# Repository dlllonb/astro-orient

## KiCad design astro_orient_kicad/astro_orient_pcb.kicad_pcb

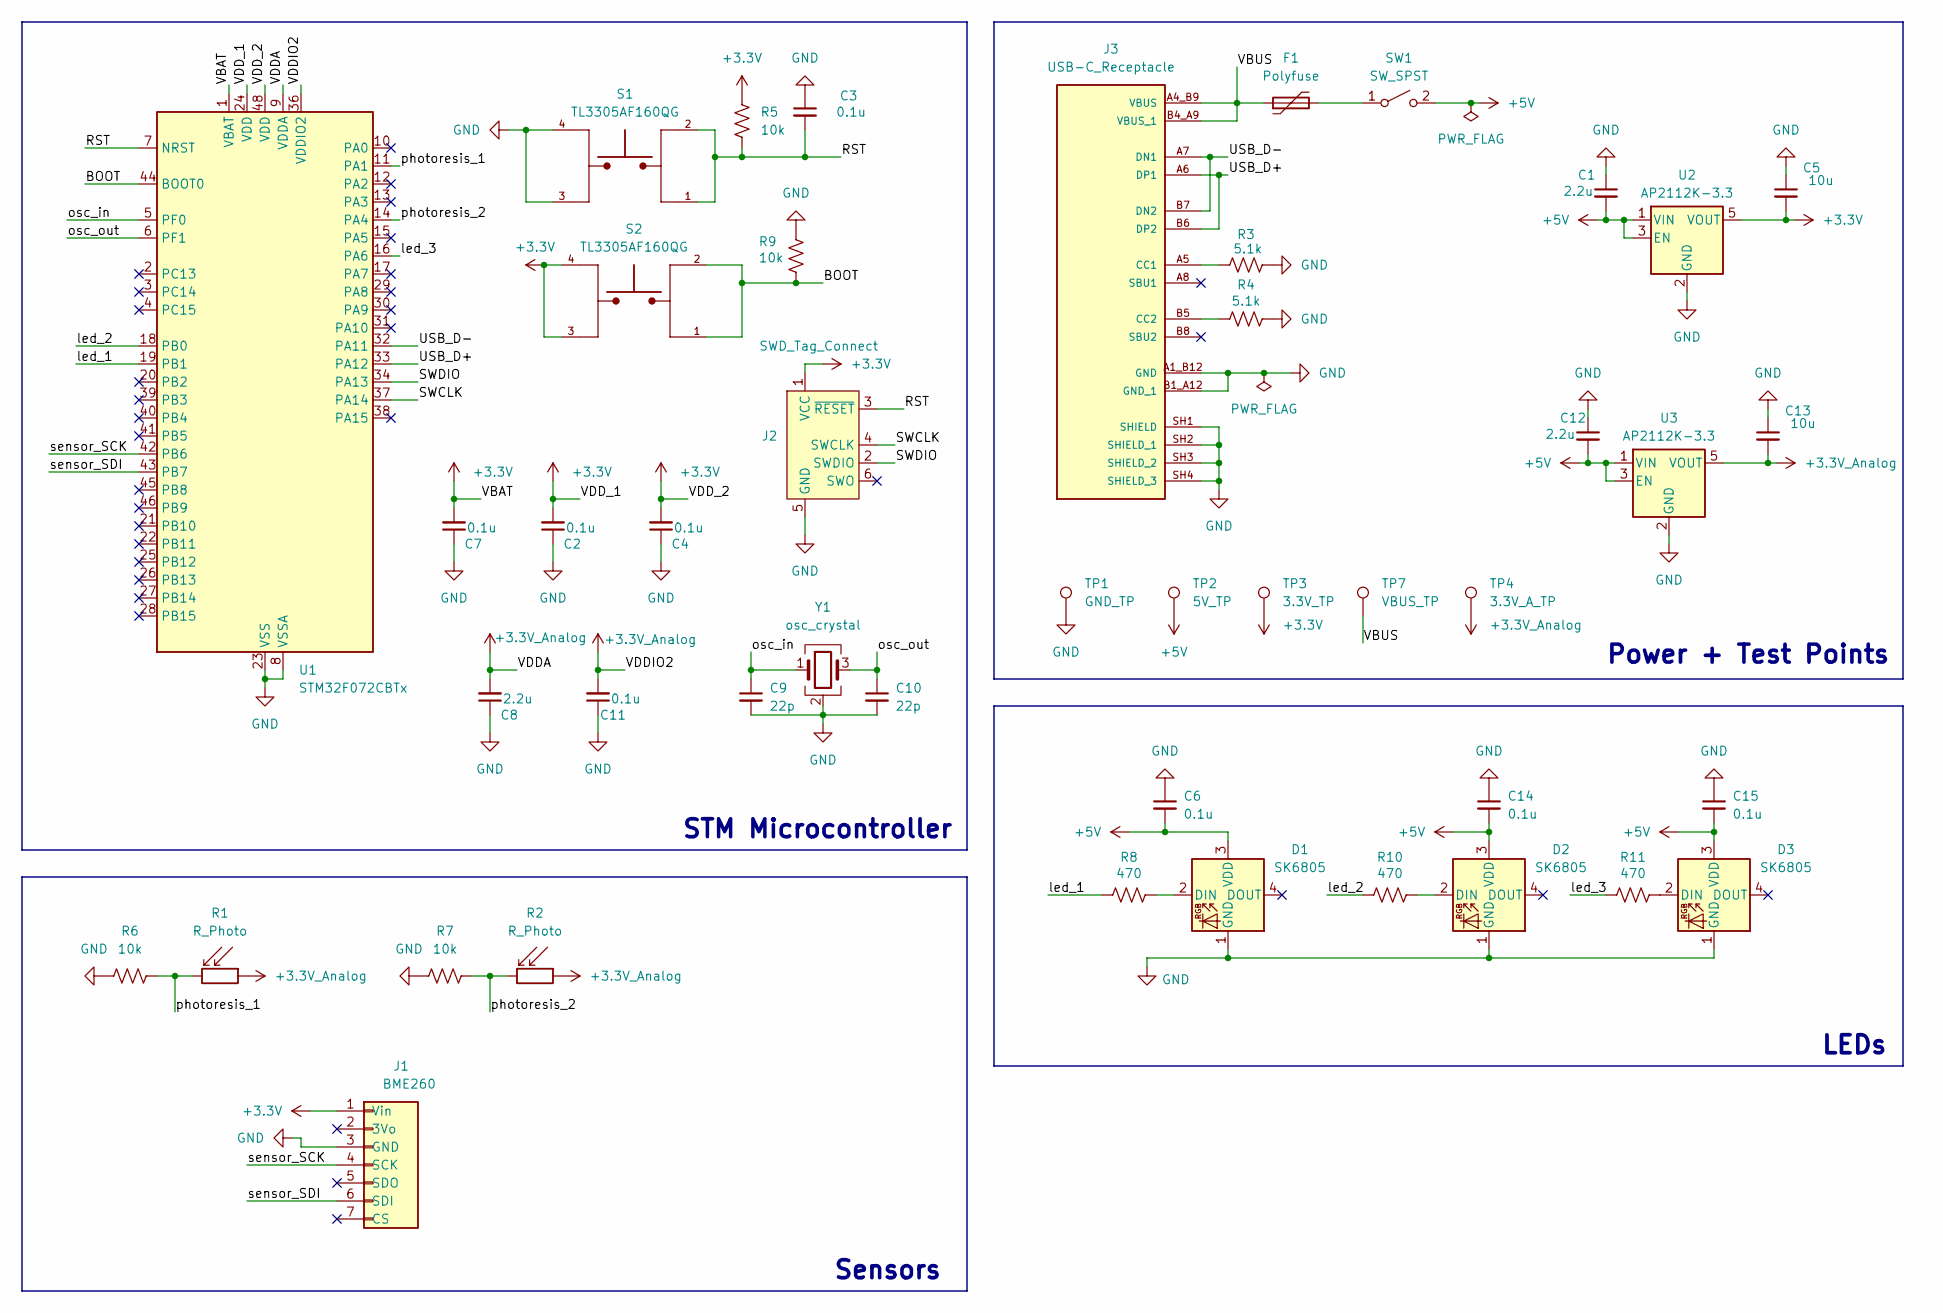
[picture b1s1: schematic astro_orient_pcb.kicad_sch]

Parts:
C1, C8, C12: 2.2u; C_0805_2012Metric
C2, C3, C4, C6, C7, C11, C14, C15: 0.1u; C_0805_2012Metric
C5, C13: 10u; C_1206_3216Metric
C9, C10: 22p; C_0805_2012Metric
D1: SK6805; LED_1655
D2, D3: SK6805; PinHeader_1x04_P2.54mm_Vertical
F1: Polyfuse; Fuse_1812_4532Metric
J1: BME260; PinHeader_1x07_P2.54mm_Vertical
J2: SWD_Tag_Connect; Tag-Connect_TC2030-IDC-FP_2x03_P1.27mm_Vertical
J3: USB-C_Receptacle; SAMESKY_UJ20-C-H-G-SMT-1-P16-TR_Correct; PARTREV 1.0
R1, R2: R_Photo; PHODET_PDV-P8103
R3, R4: 5.1k; R_0805_2012Metric
R5, R6, R7, R9: 10k; RC0805N_YAG-L
R8, R10, R11: 470; R_2512_6332Metric
S1, S2: TL3305AF160QG; SW_TL3305AF160QG; PARTREV C
SW1: SW_SPST; PinHeader_1x02_P2.54mm_Vertical
TP1: GND_TP; TestPoint_Pad_D1.0mm
TP2: 5V_TP; TestPoint_Pad_D1.0mm
TP3: 3.3V_TP; TestPoint_Pad_D1.0mm
TP4: 3.3V_A_TP; TestPoint_Pad_D1.0mm
TP7: VBUS_TP; TestPoint_Pad_D1.0mm
U1: STM32F072CBTx; LQFP-48_7x7mm_P0.5mm
U2, U3: AP2112K-3.3; SOT95P285X140-5N
Y1: osc_crystal; Crystal_SMD_Abracon_ABM3B-4Pin_5.0x3.2mm

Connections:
+3.3V: C2.2, C4.2, C5.2, C7.2, J1.1 (Vin), J2.1 (VCC), R5.1, S2.3, S2.4, TP3.1, U1.1 (VBAT), U1.24 (VDD), U1.48 (VDD), U2.5 (VOUT)
+3.3V_Analog: C8.2, C11.2, C13.2, R1.1, R2.1, TP4.1, U1.9 (VDDA), U1.36 (VDDIO2), U3.5 (VOUT)
+5V: C1.2, C6.2, C12.2, C14.2, C15.2, D1.3 (VDD), D2.3 (VDD), D3.3 (VDD), SW1.2 (B), TP2.1, U2.1 (VIN), U2.3 (EN), U3.1 (VIN), U3.3 (EN)
/BOOT: R9.2, S2.1, S2.2, U1.44 (BOOT0)
/RST: C3.2, J2.3 (~RESET), R5.2, S1.1, S1.2, U1.7 (NRST)
/SWCLK: J2.4 (SWCLK), U1.37 (PA14)
/SWDIO: J2.2 (SWDIO), U1.34 (PA13)
/USB_D+: J3.A6 (DP1), J3.B6 (DP2), U1.33 (PA12)
/USB_D-: J3.A7 (DN1), J3.B7 (DN2), U1.32 (PA11)
/VBUS: F1.1, J3.A4_B9 (VBUS), J3.B4_A9 (VBUS_1), TP7.1
/led_1: R8.1, U1.19 (PB1)
/led_2: R10.1, U1.18 (PB0)
/led_3: R11.1, U1.16 (PA6)
/osc_in: C9.1, U1.5 (PF0), Y1.1
/osc_out: C10.1, U1.6 (PF1), Y1.3
/photoresis_1: R1.2, R6.2, U1.11 (PA1)
/photoresis_2: R2.2, R7.2, U1.14 (PA4)
/sensor_SCK: J1.4 (SCK), U1.42 (PB6)
/sensor_SDI: J1.6 (SDI), U1.43 (PB7)
GND: C1.1, C2.1, C3.1, C4.1, C5.1, C6.1, C7.1, C8.1, C9.2, C10.2, C11.1, C12.1, C13.1, C14.1, C15.1, D1.1 (GND), D2.1 (GND), D3.1 (GND), J1.3 (GND), J2.5 (GND), J3.A1_B12 (GND), J3.B1_A12 (GND_1), J3.SH1 (SHIELD), J3.SH2 (SHIELD_1), J3.SH3 (SHIELD_2), J3.SH4 (SHIELD_3), R3.1, R4.1, R6.1, R7.1, R9.1, S1.3, S1.4, TP1.1, U1.8 (VSSA), U1.23 (VSS), U1.35 (VSS), U1.47 (VSS), U2.2 (GND), U3.2 (GND), Y1.2 (G), Y1.4 (G)
unnamed: D1.2 (DIN), R8.2
unnamed: D2.2 (DIN), R10.2
unnamed: D3.2 (DIN), R11.2
unnamed: J3.A5 (CC1), R3.2
unnamed: J3.B5 (CC2), R4.2
unnamed: F1.2, SW1.1 (A)

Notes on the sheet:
LEDs
Power + Test Points
Sensors
STM Microcontroller

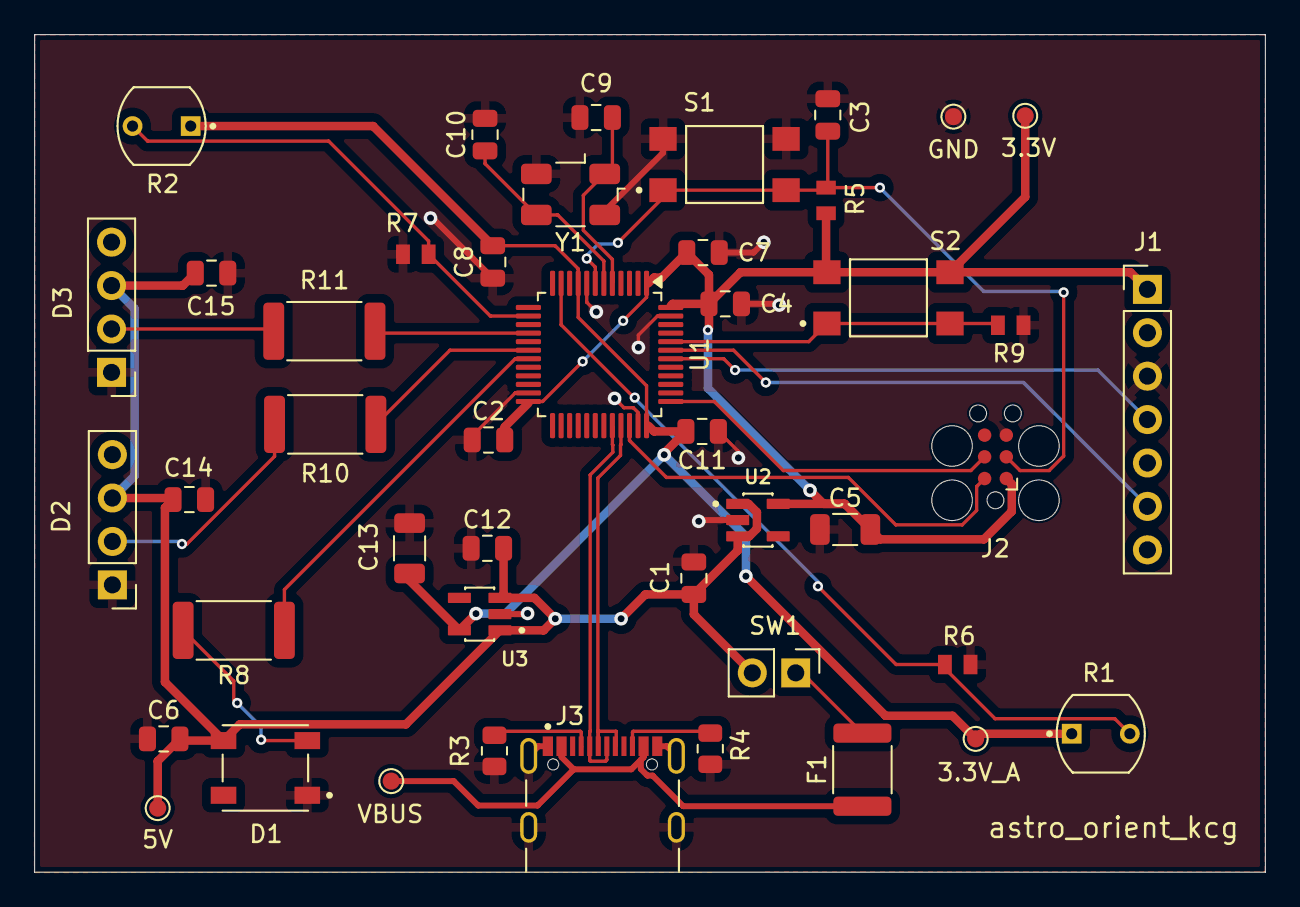
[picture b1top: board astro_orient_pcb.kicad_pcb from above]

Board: 2 copper layers, 72.0 x 49.0 mm, 45 parts (0 on the bottom side), 26 nets.

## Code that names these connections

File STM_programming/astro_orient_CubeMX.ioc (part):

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Mcu.Name=STM32F072C(8-B)Tx
Mcu.Package=LQFP48
Mcu.UserName=STM32F072CBTx
PB1.GPIOParameters=GPIO_Speed,PinState,GPIO_Label
PB1.GPIO_Label=LED1_DATA
PB1.GPIO_Speed=GPIO_SPEED_FREQ_HIGH
PB1.PinState=GPIO_PIN_RESET
PB1.Signal=GPIO_Output
PF0-OSC_IN.Mode=HSE-External-Oscillator
PF0-OSC_IN.Signal=RCC_OSC_IN
PF1-OSC_OUT.Mode=HSE-External-Oscillator
PF1-OSC_OUT.Signal=RCC_OSC_OUT
RCC.SYSCLKFreq_VALUE=48000000
RCC.SYSCLKSource=RCC_SYSCLKSOURCE_PLLCLK
board=custom

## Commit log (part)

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2026-05-04 setting up notes files
2026-05-04 wrote todo list
2026-05-04 update todo
2026-05-07 Test push
2026-05-08 note on DKRed
2026-05-19 edit
2026-05-27 update kicad folder, sort previous issues
2026-05-27 started creating schematic for PCB
2026-05-31 completed initial schematic, missing test pins
2026-06-01 Testing how IMU module works
2026-06-01 Updated PCB schematic and created test files for GPS module
2026-06-01 Updated PCB schematic
2026-06-02 Testing with interpreting GPS data
2026-06-03 Fixed kicad electrical rules errors. schematic should be complete
2026-06-03 made classes to read and store relevant gps data
2026-06-10 updated footprints on PCB
2026-06-15 updated schematic, partial layout of PCB
2026-06-17 completed layout of schematic
2026-06-30 last changes to PCB
2026-06-30 Partial work on GUI
